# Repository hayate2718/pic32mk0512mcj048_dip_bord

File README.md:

# pic32mk0512mcj048_dip_bord
## 仕様
1. PIC32MK0512MCJ048のDIP化基板
2. 振動子などの最低限必要な外部回路を搭載する
3. 書き込み端子以外の汎用IOをすべて使用可にする
4. CANトランシーバ搭載、LED搭載
5. メインオシレータ16MHz
6. セカンダリオシレータ32.768KHz

ReservedPin

|Number|Name|Function|
|---|---|---|
|4|MCLR|MCLR|
|5|VSS|VSS|
|6|VDD|VDD|
|11|RB0|**VREF-**|
|12|RB1|**VREF+**|
|15|AVDD|AVDD|
|16|AVSS|AVSS|
|21|VSS|VSS|
|22|VDD|VDD|
|25|RA4|**C1RX**|
|26|VDD|VDD|
|27|RC12|**OSCI**|
|28|RC15|**OSCO**|
|29|VSS|VSS|
|30|RD8|**LED_R**|
|31|RB5|**PGD2**|
|32|RB6|**PGC2**|
|33|RC10|**LED_G**|
|34|RB7|**C1TX**|
|35|RC13|**SOSCI**|
|36|RB8|**SOSCO**|
|42|VSS|VSS|
|43|VDD|VDD|

## エラッタ
Harmony V3 でコードを出力して、PLIBを使ったときに出力されたコードを書き換えないとうまく動作しないことがあった。<br>
その対処を記録しておく。

### コンパイラの最適化
割り込みハンドラと共有する変数に`volatile`修飾子をつける。

### SPI slave
受信割り込みハンドラ内でSPIxBUFが一回目の読み取り以降変化しない。<br>
対処:SPIxBUFに書き込みを行いSPIxBUFをクリアする。<br>
以下例
```c++
void SPI2_RX_InterruptHandler (void)
{
    uint32_t receivedData = 0;

    spi2Obj.rxInterruptActive = true;

    while (!(SPI2STAT & _SPI2STAT_SPIRBE_MASK))
    {
        /* Receive buffer is not empty. Read the received data. */
        receivedData = SPI2BUF;
        
        memset((void*)&SPI2BUF,0,sizeof(SPI2BUF)); //add code

        if (spi2Obj.rdInIndex < SPI2_READ_BUFFER_SIZE)
        {
            SPI2_ReadBuffer[spi2Obj.rdInIndex++] = receivedData;
        }
    }

    /* Clear the receive interrupt flag */
    SPI2_CLEAR_RX_INT_FLAG();

    spi2Obj.rxInterruptActive = false;

    /* Check if CS interrupt occured before the RX interrupt and that CS interrupt delegated the responsibility to give
     * application callback to the RX interrupt */

    if (spi2Obj.csInterruptPending == true)
    {
        spi2Obj.csInterruptPending = false;
        spi2Obj.transferIsBusy = false;

        spi2Obj.wrOutIndex = 0;
        spi2Obj.nWrBytes = 0;

        if(spi2Obj.callback != NULL)
        {
            spi2Obj.callback(spi2Obj.context);
        }

        /* Clear the read index. Application must read out the data by calling SPI2_Read API in the callback */
        spi2Obj.rdInIndex = 0;
    }
}
```
## 考え中
<b>
PINネームを大きめに入れたい<br>
LED駆動用FETをプルダウンする<br>
IO引き出し線をもう少し太くしたい<br>
在庫があればCANトラをSOICにしたい<br>
redemi が長くなりすぎたらwikiにまとめる。
</b>

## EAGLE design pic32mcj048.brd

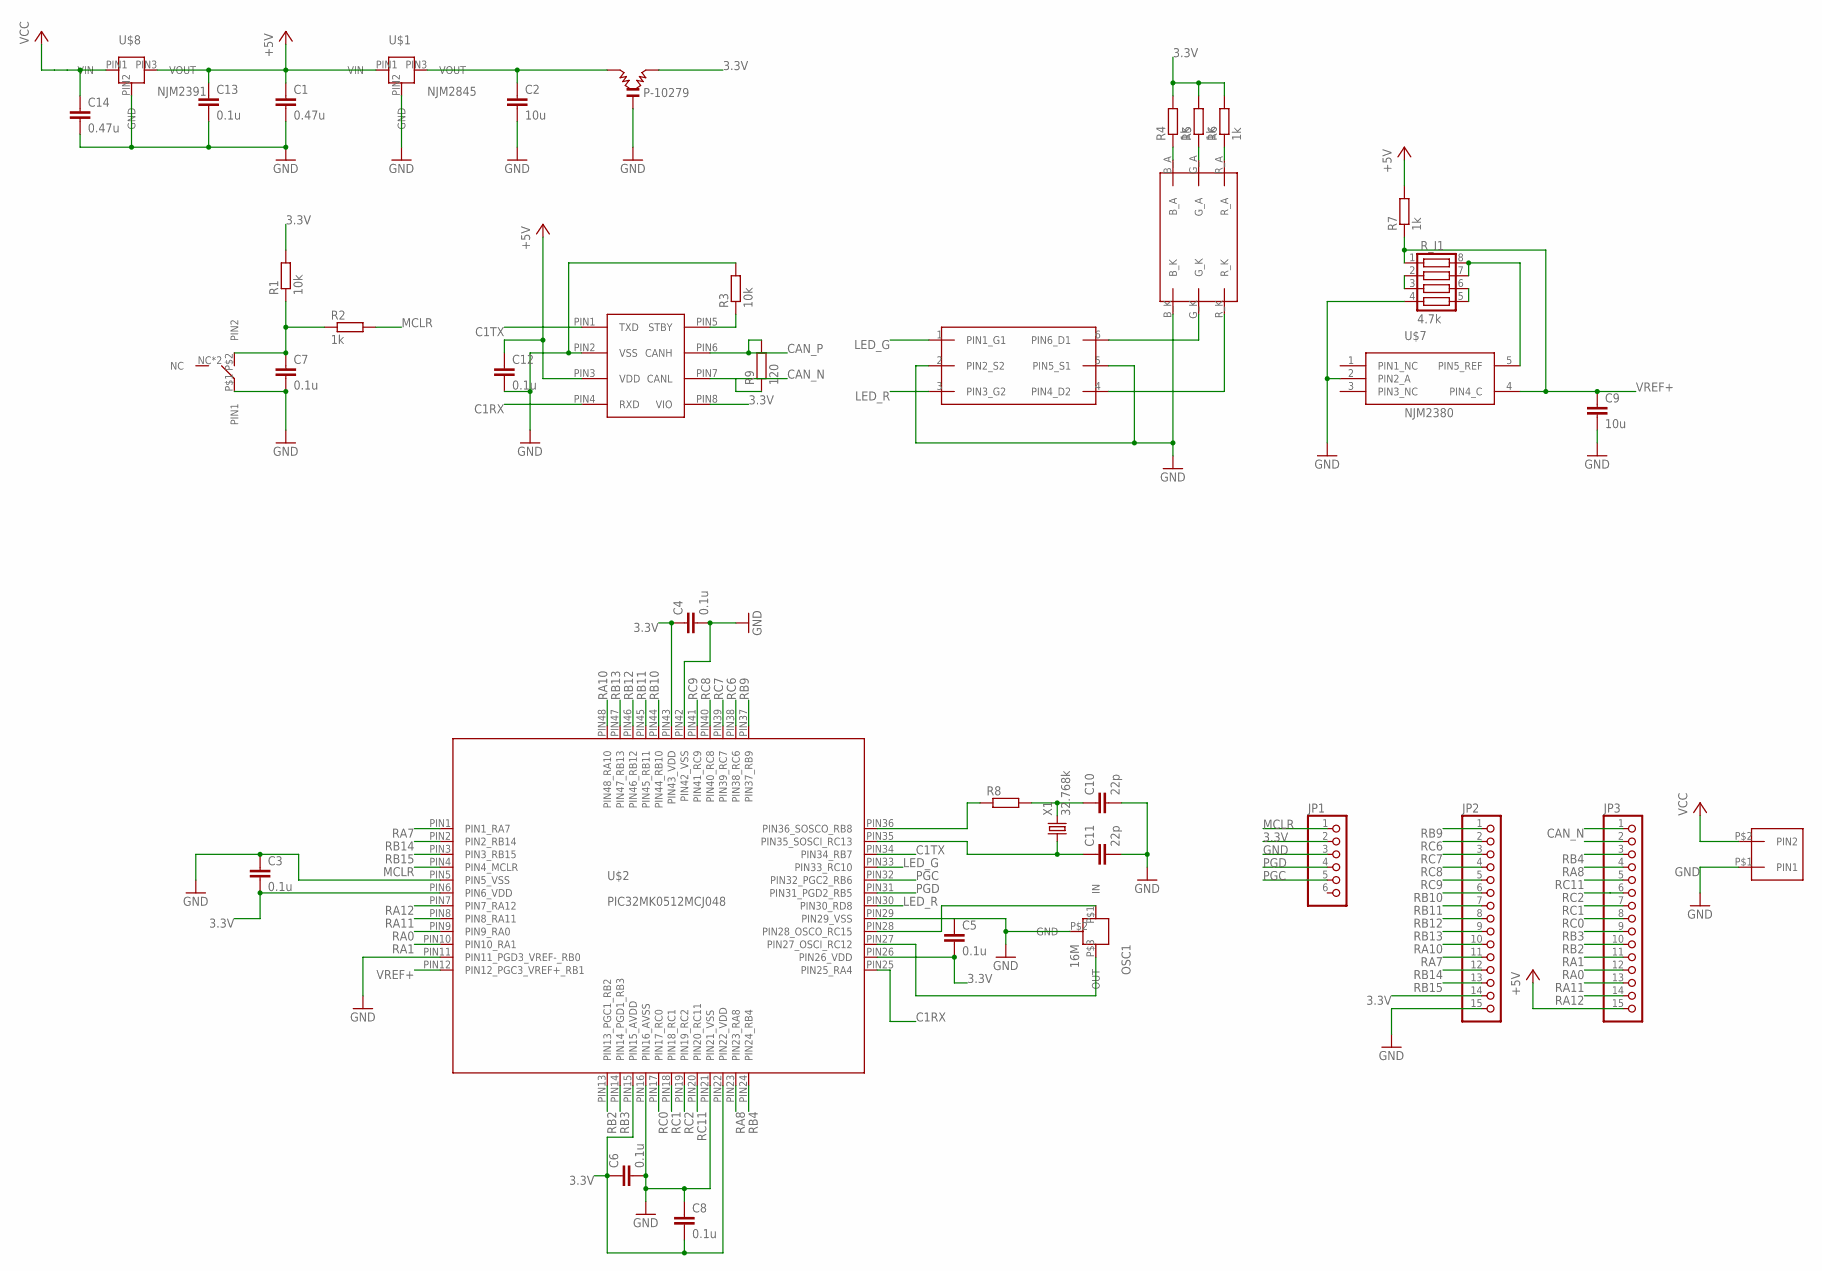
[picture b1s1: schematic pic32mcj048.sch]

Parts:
C1, C14: 0.47u; C1608
C2, C9: 10u; C1608
C3, C4, C5, C6, C7, C8, C12, C13: 0.1u; C1608
C10, C11: 22p; C1608
IC1: MCP2562; DIL8
JP1: PINHD-1X6; 1X06
JP2, JP3: PINHD-1X15; 1X15
OSC1: 16M; CSTNE#
P-10279: LCL
R1, R3: 10k; 1608
R2, R4, R5, R6, R7: 1k; 1608
R8: R_REG; 1608
R9: 120; 1608
R_I1: 4.7k; 1005X4RESISTOR
U$1: NJM2845; TO252
U$2: PIC32MK0512MCJ048; LQFP48PIN
U$3: TAKUTOSUITTI2
U$4: XH_2P
U$5: RGB_LED
U$6: FDC6305; SSOT6
U$7: NJM2380; SOT23-5
U$8: NJM2391; TO252
X1: 32.768k; FC255

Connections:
3.3V: C3.2, C4.1, C5.2, C6.1, C8.2, IC1.PIN8 (VIO), JP1.2, JP2.14, P-10279.2, R1.2, R4.2, R5.2, R6.2, U$2.PIN6 (PIN6_VDD), U$2.PIN15 (PIN15_AVDD), U$2.PIN22 (PIN22_VDD), U$2.PIN26 (PIN26_VDD), U$2.PIN43 (PIN43_VDD)
+5V: C1.1, C12.1, C13.1, IC1.PIN3 (VDD), JP3.15, R7.2, U$1.PIN1 (VIN), U$8.PIN3 (VOUT)
C1RX: IC1.PIN4 (RXD), U$2.PIN25 (PIN25_RA4)
C1TX: IC1.PIN1 (TXD), U$2.PIN34 (PIN34_RB7)
CAN_N: IC1.PIN7 (CANL), JP3.1, R9.1
CAN_P: IC1.PIN6 (CANH), JP3.2, R9.2
GND: C1.2, C2.2, C3.1, C4.2, C5.1, C6.2, C7.2, C8.1, C9.2, C10.2, C11.2, C12.2, C13.2, C14.2, IC1.PIN2 (VSS), JP1.3, JP2.15, OSC1.P$2 (GND), P-10279.0 (GND), R3.2, R_I1.4, U$1.PIN2 (GND), U$2.PIN5 (PIN5_VSS), U$2.PIN11 (PIN11_PGD3_VREF-_RB0), U$2.PIN16 (PIN16_AVSS), U$2.PIN21 (PIN21_VSS), U$2.PIN29 (PIN29_VSS), U$2.PIN42 (PIN42_VSS), U$3.P$1 (PIN1), U$4.P$1 (PIN1), U$5.B_K, U$6.2 (PIN2_S2), U$6.5 (PIN5_S1), U$7.2 (PIN2_A), U$8.PIN2 (GND)
LED_G: U$2.PIN33 (PIN33_RC10), U$6.1 (PIN1_G1)
LED_R: U$2.PIN30 (PIN30_RD8), U$6.3 (PIN3_G2)
MCLR: JP1.1, R2.2, U$2.PIN4 (PIN4_MCLR)
unnamed: C2.1, P-10279.1, U$1.PIN3 (VOUT)
unnamed: C7.1, R1.1, R2.1, U$3.P$2 (PIN2)
unnamed: OSC1.P$1 (IN), U$2.PIN28 (PIN28_OSCO_RC15)
unnamed: OSC1.P$3 (OUT), U$2.PIN27 (PIN27_OSCI_RC12)
unnamed: IC1.PIN5 (STBY), R3.1
unnamed: C10.1, R8.2, X1.P$2 (2)
unnamed: C11.1, U$2.PIN35 (PIN35_SOSCI_RC13), X1.P$1 (1)
unnamed: U$5.G_K, U$6.6 (PIN6_D1)
unnamed: U$5.R_K, U$6.4 (PIN4_D2)
unnamed: R8.1, U$2.PIN36 (PIN36_SOSCO_RB8)
unnamed: R4.1, U$5.B_A
unnamed: R5.1, U$5.G_A
unnamed: R6.1, U$5.R_A
unnamed: R_I1.7, R_I1.8, U$7.5 (PIN5_REF)
unnamed: R_I1.2, R_I1.3
unnamed: R_I1.5, R_I1.6
PGC: JP1.5, U$2.PIN32 (PIN32_PGC2_RB6)
PGD: JP1.4, U$2.PIN31 (PIN31_PGD2_RB5)
RA0: JP3.12, U$2.PIN9 (PIN9_RA0)
RA1: JP3.11, U$2.PIN10 (PIN10_RA1)
RA7: JP2.11, U$2.PIN1 (PIN1_RA7)
RA8: JP3.4, U$2.PIN23 (PIN23_RA8)
RA10: JP2.10, U$2.PIN48 (PIN48_RA10)
RA11: JP3.13, U$2.PIN8 (PIN8_RA11)
RA12: JP3.14, U$2.PIN7 (PIN7_RA12)
RB2: JP3.10, U$2.PIN13 (PIN13_PGC1_RB2)
RB3: JP3.9, U$2.PIN14 (PIN14_PGD1_RB3)
RB4: JP3.3, U$2.PIN24 (PIN24_RB4)
RB9: JP2.1, U$2.PIN37 (PIN37_RB9)
RB10: JP2.6, U$2.PIN44 (PIN44_RB10)
RB11: JP2.7, U$2.PIN45 (PIN45_RB11)
RB12: JP2.8, U$2.PIN46 (PIN46_RB12)
RB13: JP2.9, U$2.PIN47 (PIN47_RB13)
RB14: JP2.12, U$2.PIN2 (PIN2_RB14)
RB15: JP2.13, U$2.PIN3 (PIN3_RB15)
RC0: JP3.8, U$2.PIN17 (PIN17_RC0)
RC1: JP3.7, U$2.PIN18 (PIN18_RC1)
RC2: JP3.6, U$2.PIN19 (PIN19_RC2)
RC6: JP2.2, U$2.PIN38 (PIN38_RC6)
RC7: JP2.3, U$2.PIN39 (PIN39_RC7)
RC8: JP2.4, U$2.PIN40 (PIN40_RC8)
RC9: JP2.5, U$2.PIN41 (PIN41_RC9)
RC11: JP3.5, U$2.PIN20 (PIN20_RC11)
VCC: C14.1, U$4.P$2 (PIN2), U$8.PIN1 (VIN)
VREF+: C9.1, R7.1, R_I1.1, U$2.PIN12 (PIN12_PGC3_VREF+_RB1), U$7.4 (PIN4_C)

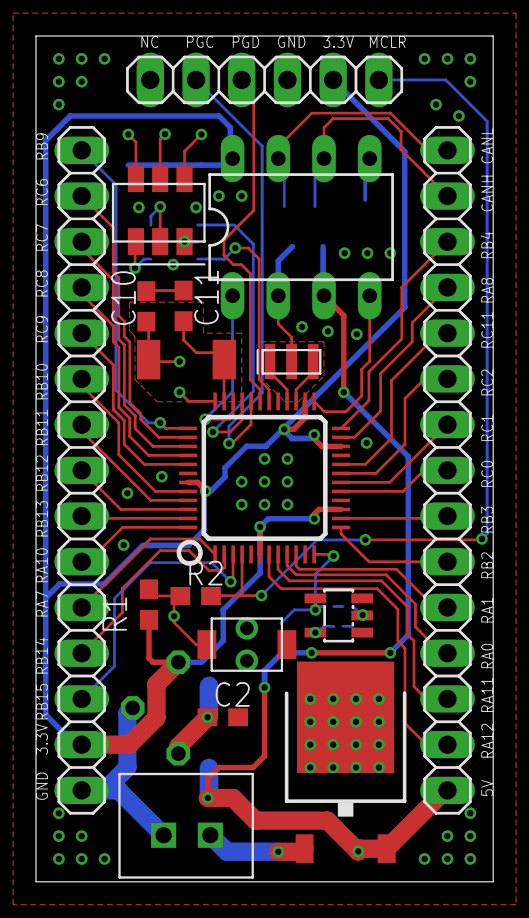
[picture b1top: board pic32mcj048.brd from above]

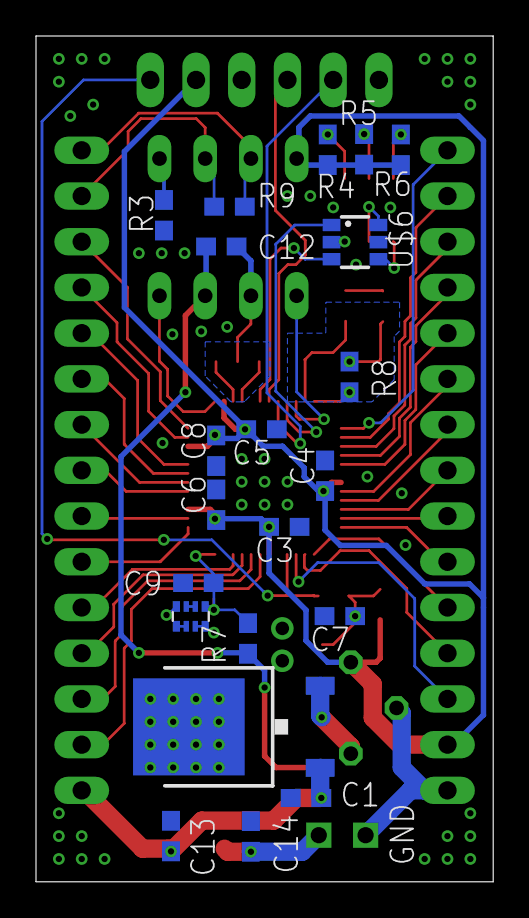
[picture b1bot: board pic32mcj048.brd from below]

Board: 2 copper layers, 25.4 x 47.0 mm, 39 parts (21 on the bottom side), 55 nets.

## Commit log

2021-02-25 ファイル作成
2021-02-25 ignoreのついか
2021-02-25 リセット回路、書き込み回路を作った
2021-07-27 brdfileを編集
2021-08-13 sch完成
2021-08-23 hoge
2021-09-24 基本設計完了、あとは調整など
2021-09-28 完成、ガーバーデータ追加
2021-11-09 mcp2562スタンバイピンプルダウン
